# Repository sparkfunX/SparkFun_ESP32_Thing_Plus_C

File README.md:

SparkFun ESP32 Thing Plus C
========================================

[*SparkFun ESP32 Thing Plus C (SPX-18018)*](https://www.sparkfun.com/products/18018)

The [SparkFun ESP32 Thing Plus C](https://www.sparkfun.com/products/18018) is a comprehensive development platform for [Espressif's ESP32](https://espressif.com/en/products/hardware/esp32/overview). Like the 8266 and ESP32 Thing, the ESP32 Thing Plus is a **WiFi**-compatible microcontroller with support for both **Bluetooth Classic** (i.e. SPP) and **Bluetooth low-energy** (i.e. BLE, BT4.0, Bluetooth Smart), a Qwiic connector, and 21 I/O pins. Add to that a rich set of peripherals ranging from capacitive touch sensors, Hall sensors, SD card interface, Ethernet, high-speed SPIs, UARTs, I2S and I<sup>2</sup>C.

We took all the good from the original [ESP32 Thing Plus](https://www.sparkfun.com/products/15663) and sprinkled on some more! USB C provides up to 2A, upgraded 16MB flash ESP32 WROOM module, CH340 USB to serial IC, an onboard fuel gauge IC will make sure you know your battery levels, and an onboard addressable LED is perfect for as a multi-status LED. Oh, and the new taller reset and boot buttons are *so* much easier to push!

We added a dedicator regulator to the Qwiic connector to enable software power control of the Qwiic bus - great for low power logging! There's even a microSD connector on the back!

The ESP32 Thing plus integrates a rich set of peripherals, ranging from capacitive touch sensors, Hall sensors, SD card interface, Ethernet, high-speed SPI, UART, I2S and I2C. Thanks to the onboard ESP32 WROOM module, the SparkFun Thing Plus features 16MB of flash memory, 520kB of internal SRAM, an integrated 802.11 BGN WiFi transceiver and dual-mode Bluetooth capabilities, and a JST connector to plug in a LiPo battery.

For programming, select the 'ESP32 Dev Module'. This will get you direct pin to pin access to each of the WROOM's pins.

Repository Contents
-------------------

* **/Hardware** - Eagle design files (.brd, .sch)
* **/Firmware** - Example sketches demostrating extra peripherals

License Information
-------------------

This product is _**open source**_! 

Please review the LICENSE.md file for license information. 

If you have any questions or concerns on licensing, please contact technical support on our [SparkFun forums](https://forum.sparkfun.com/viewforum.php?f=152).

Distributed as-is; no warranty is given.

- Your friends at SparkFun.

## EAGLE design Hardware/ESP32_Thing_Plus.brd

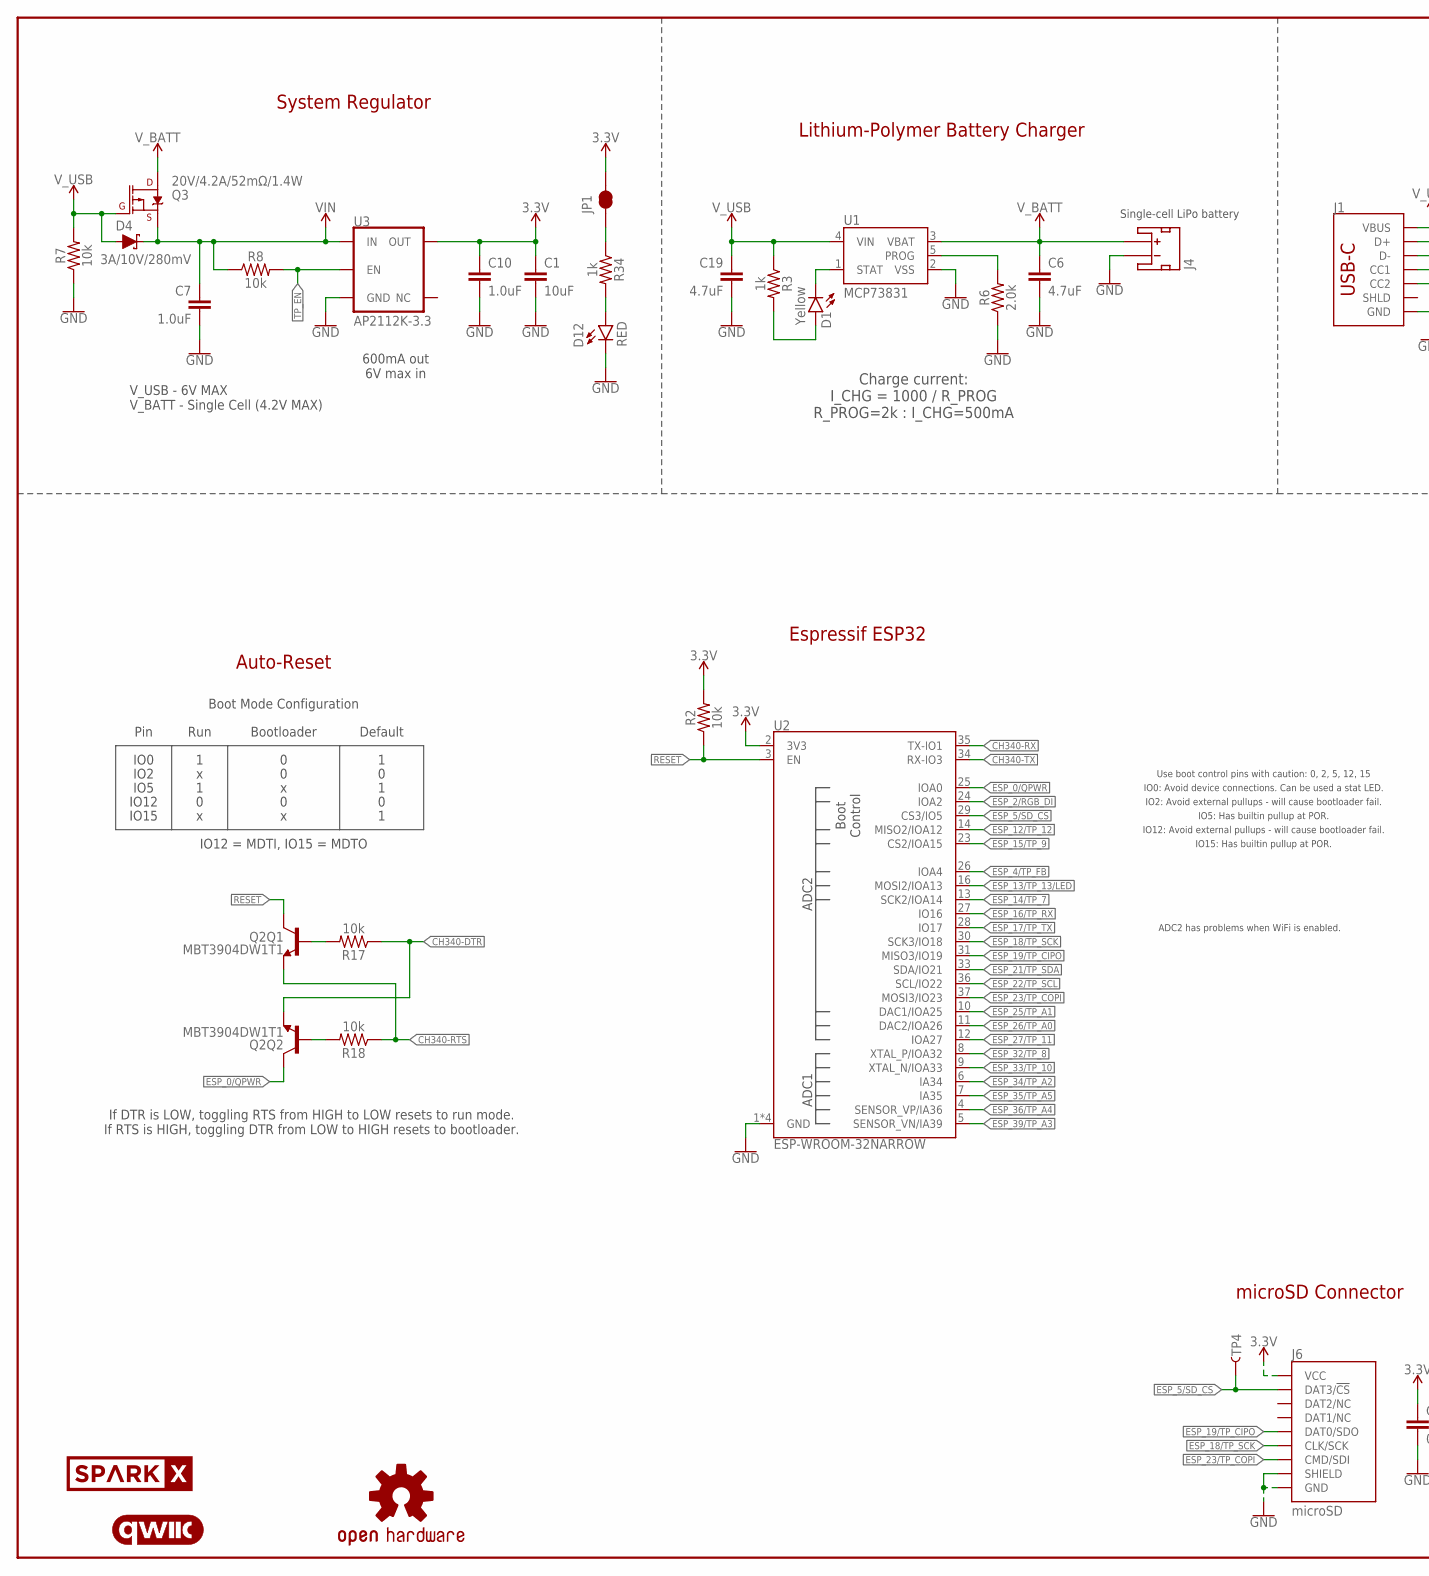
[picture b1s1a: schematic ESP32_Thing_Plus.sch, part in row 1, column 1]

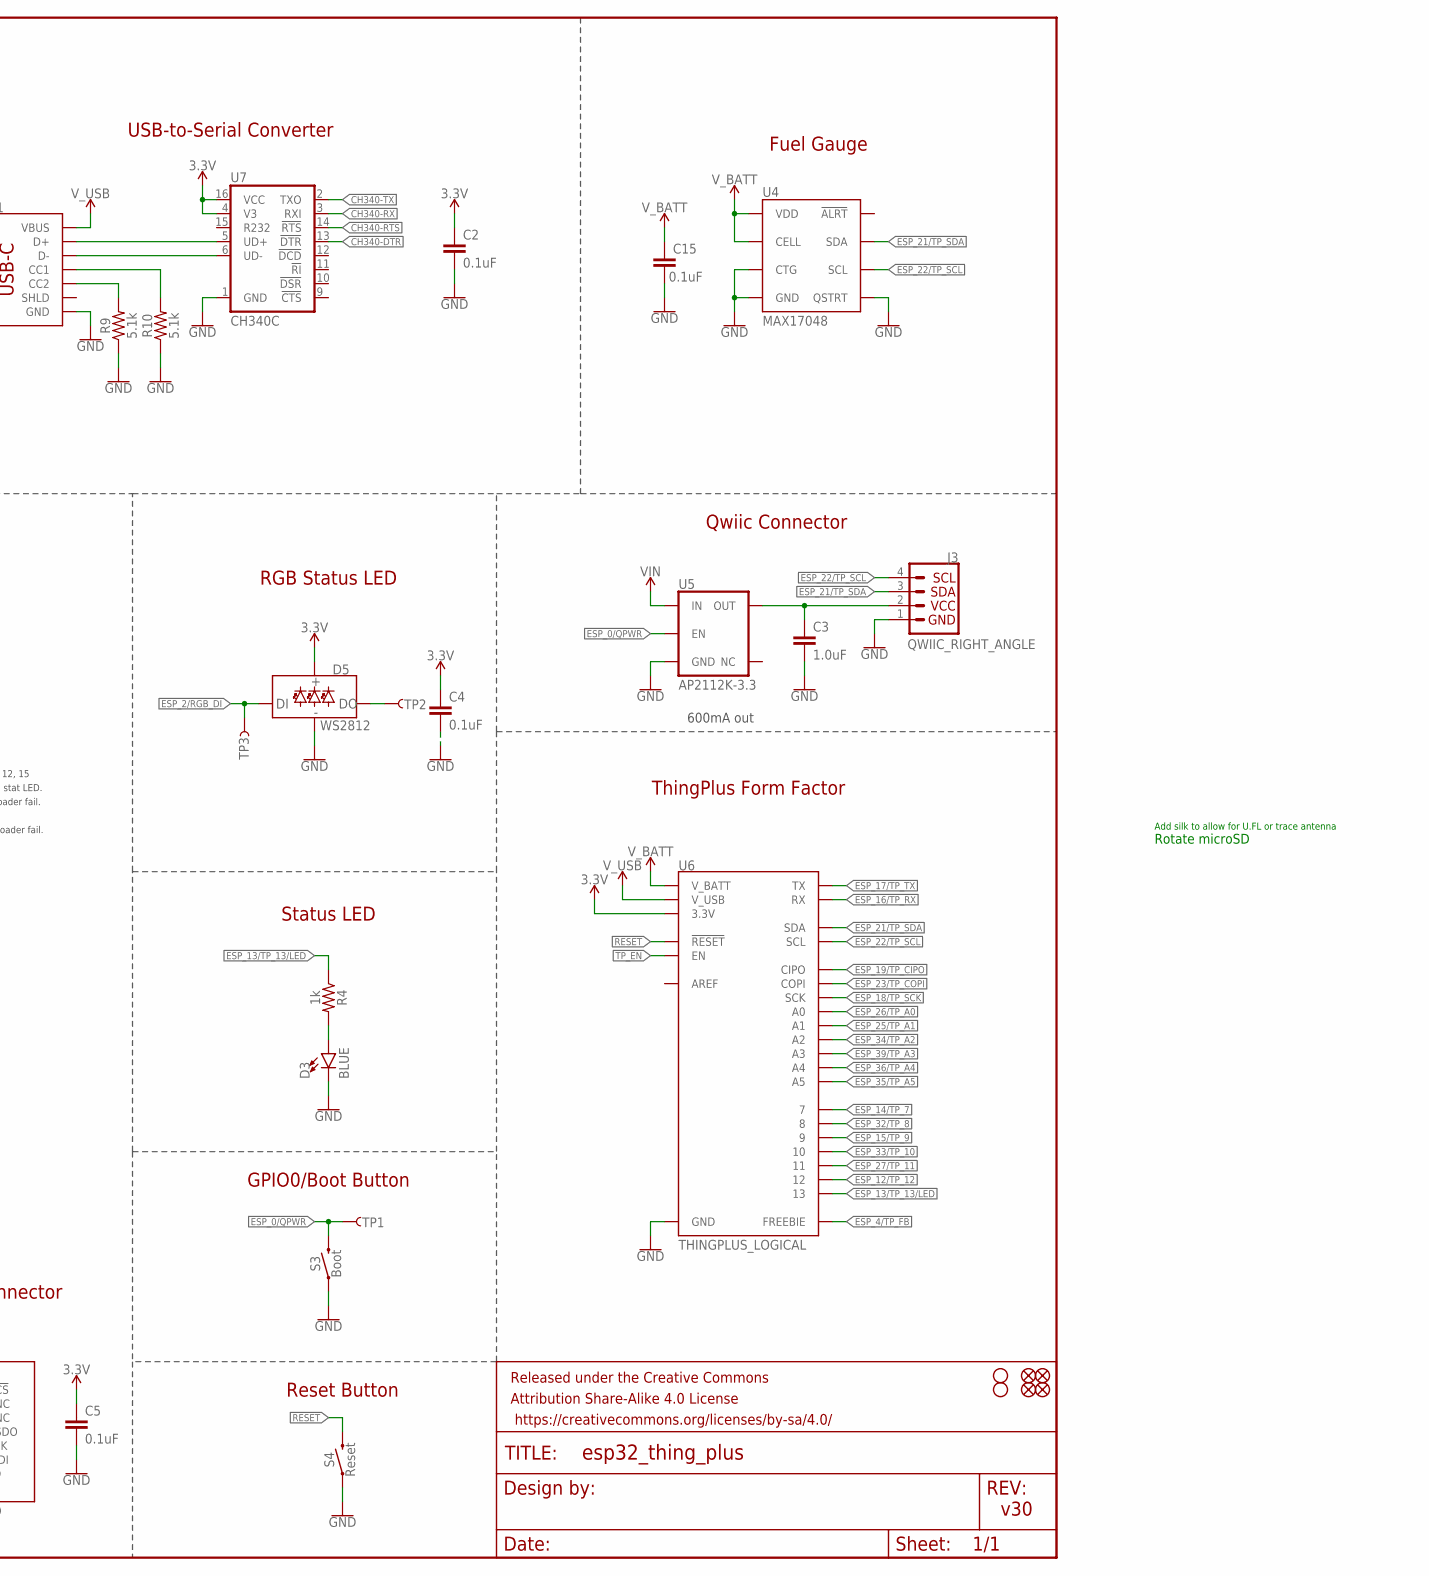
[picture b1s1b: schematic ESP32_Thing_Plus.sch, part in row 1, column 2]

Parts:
C1: 10uF; 0402-TIGHT
C2, C4, C5, C15: 0.1uF; 0402-TIGHT
C3, C7, C10: 1.0uF; 0402-TIGHT
C6: 4.7uF; 0402-TIGHT
C19: 4.7uF; 0603
D1: Yellow; LED-0603
D3: BLUE; LED-0603
D4: 3A/10V/280mV; SOD-323
D5: WS2812; WS2812-2020
D12: RED; LED-0603
FD1, FD2, FD3, FD4: FIDUCIALUFIDUCIAL; FIDUCIAL-MICRO
FRAME1: FRAME-LEDGER; CREATIVE_COMMONS
H1, H2: STAND-OFFTIGHT; STAND-OFF-TIGHT
J1: USB_C_2-LAYER_PADS; USB-C-16P-2LAYER-PADS
J3: QWIIC_RIGHT_ANGLE; JST04_1MM_RA
J4: JST_2MM_MALE; JST-2-SMD
J6: microSD; MICRO-SD-SOCKET
JP1: JUMPER-SMT_2_NC_TRACE_SILK; SMT-JUMPER_2_NC_TRACE_SILK
LOGO2: OSHW-LOGOMINI; OSHW-LOGO-MINI
LOGO4: QWIIC_LOGO_4MM; QWIIC_4MM
Q2: MBT3904DW1T1; SC70-6
Q3: 20V/4.2A/52mΩ/1.4W; SOT23-3
R2, R7, R8, R17, R18: 10k; 0402-TIGHT
R3, R4, R34: 1k; 0402-TIGHT
R6: 2.0k; 0603
R9, R10: 5.1k; 0402-TIGHT
S3: Boot; TACTILE_SWITCH_SMD_4.6X2.8MM
S4: Reset; TACTILE_SWITCH_SMD_4.6X2.8MM
TP1, TP2, TP3, TP4: TEST-POINT3X5; PAD.03X.05
U1: MCP73831; SOT23-5
U2: ESP-WROOM-32NARROW; ESP-WROOM-32-NARROW
U3, U5: AP2112K-3.3; SOT23-5
U4: MAX17048; DFN-8
U6: THINGPLUS_LOGICAL; THINGPLUS_FOOTPRINT
U7: CH340C; SO016
U$1: SPARKX-LOGO4; SPARKX-MEDIUM

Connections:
3.3V: C1.1, C2.1, C4.1, C5.1, C10.1, D5.VCC, J6.VCC, JP1.2, R2.2, U2.2 (3V3), U3.5 (OUT), U6.3V3 (3.3V), U7.4 (V3), U7.16 (VCC)
!RESET!: Q2.3 (C), R2.1, S4.3 (2), S4.4 (2), U2.3 (EN), U6.RST (!RESET)
CH340-DTR: Q2.1 (E), R17.1, U7.13 (!DTR)
CH340-RTS: Q2.4 (E), R18.1, U7.14 (!RTS)
CH340-RX: U2.35 (TX-IO1), U7.3 (RXI)
CH340-TX: U2.34 (RX-IO3), U7.2 (TXO)
CHG: D1.C, U1.1 (STAT)
CHG_LED: D1.A, R3.2
D+: J1.A6 (D+), J1.B6 (D+), U7.5 (UD+)
D-: J1.A7 (D-), J1.B7 (D-), U7.6 (UD-)
DTR-10K: Q2.5 (B), R17.2
ESP_0/QPWR: Q2.6 (C), S3.3 (2), S3.4 (2), TP1.P$1, U2.25 (IOA0), U5.3 (EN)
ESP_2/RGB_DI: D5.DI, TP3.P$1, U2.24 (IOA2)
ESP_4/TP_FB: U2.26 (IOA4), U6.FREEBIE
ESP_5/SD_CS: J6.CS/DAT3 (DAT3/!CS!), TP4.P$1, U2.29 (CS3/IO5)
ESP_12/TP_12: U2.14 (MISO2/IOA12), U6.12
ESP_13/TP_13/LED: R4.1, U2.16 (MOSI2/IOA13), U6.13
ESP_14/TP_7: U2.13 (SCK2/IOA14), U6.7
ESP_15/TP_9: U2.23 (CS2/IOA15), U6.9
ESP_16/TP_RX: U2.27 (IO16), U6.RX
ESP_17/TP_TX: U2.28 (IO17), U6.TX
ESP_18/TP_SCK: J6.SCLK (CLK/SCK), U2.30 (SCK3/IO18), U6.SCK
ESP_19/TP_CIPO: J6.DO/DAT0 (DAT0/SDO), U2.31 (MISO3/IO19), U6.CIPO
ESP_21/TP_SDA: J3.3, U2.33 (SDA/IO21), U4.8 (SDA), U6.SDA
ESP_22/TP_SCL: J3.4, U2.36 (SCL/IO22), U4.7 (SCL), U6.SCL
ESP_23/TP_COPI: J6.DI/CMD (CMD/SDI), U2.37 (MOSI3/IO23), U6.COPI
ESP_25/TP_A1: U2.10 (DAC1/IOA25), U6.A1
ESP_26/TP_A0: U2.11 (DAC2/IOA26), U6.A0
ESP_27/TP_11: U2.12 (IOA27), U6.11
ESP_32/TP_8: U2.8 (XTAL_P/IOA32), U6.8
ESP_33/TP_10: U2.9 (XTAL_N/IOA33), U6.10
ESP_34/TP_A2: U2.6 (IA34), U6.A2
ESP_35/TP_A5: U2.7 (IA35), U6.A5
ESP_36/TP_A4: U2.4 (SENSOR_VP/IA36), U6.A4
ESP_39/TP_A3: U2.5 (SENSOR_VN/IA39), U6.A3
GND: C1.2, C2.2, C3.2, C4.2, C5.2, C6.2, C7.2, C10.2, C15.2, C19.2, D3.C, D5.GND, D12.C, J1.GND, J1.GND2 (GND), J3.1, J4.1 (-), J6.CD1 (SHIELD), J6.GND, J6.GND1 (GND), J6.GND3 (GND), R6.1, R7.1, R9.1, R10.1, S3.1, S3.2 (1), S4.1, S4.2 (1), U1.2 (VSS), U2.1 (GND), U2.15 (GND), U2.38 (GND), U2.GND, U3.2 (GND), U4.1 (CTG), U4.4 (GND), U4.6 (QSTRT), U4.9 (GND), U5.2 (GND), U6.GND, U7.1 (GND)
unnamed: JP1.1, R34.1
unnamed: D3.A, R4.2
unnamed: D5.DO, TP2.P$1
unnamed: J1.B5 (CC2), R9.2
unnamed: J1.A5 (CC1), R10.2
unnamed: R6.2, U1.5 (PROG)
unnamed: D12.A, R34.2
QWIIC_PWR: C3.1, J3.2, U5.5 (OUT)
RTS-10K: Q2.2 (B), R18.2
TP_EN: R8.2, U3.3 (EN), U6.EN
VIN: C7.1, D4.C, Q3.2 (S), R8.1, U3.1 (IN), U5.1 (IN)
V_BATT: C6.1, C15.1, J4.2 (+), Q3.3 (D), U1.3 (VBAT), U4.2 (CELL), U4.3 (VDD), U6.V_BATT
V_USB: C19.1, D4.A, J1.VBUS1 (VBUS), J1.VBUS2 (VBUS), Q3.1 (G), R3.1, R7.2, U1.4 (VIN), U6.V_USB

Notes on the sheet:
USB-to-Serial Converter
Single-cell LiPo battery
Charge current: I_CHG = 1000 / R_PROG R_PROG=2k : I_CHG=500mA
System Regulator
Lithium-Polymer Battery Charger
600mA out 6V max in
Auto-Reset
Espressif ESP32
Reset Button
ThingPlus Form Factor
v30
If DTR is LOW, toggling RTS from HIGH to LOW resets to run mode. If RTS is HIGH, toggling DTR from LOW to HIGH resets to bootloader.
Qwiic Connector
Status LED
GPIO0/Boot Button
V_USB - 6V MAX V_BATT - Single Cell (4.2V MAX)
Pin
IO0
IO2
IO12
IO15
IO5
Run
Bootloader
Default
IO12 = MDTI, IO15 = MDTO
Boot Mode Configuration
IO0: Avoid device connections. Can be used a stat LED.
ADC2 has problems when WiFi is enabled.
IO12: Avoid external pullups - will cause bootloader fail.
Use boot control pins with caution: 0, 2, 5, 12, 15
IO2: Avoid external pullups - will cause bootloader fail.
Fuel Gauge
600mA out
RGB Status LED
microSD Connector
Add silk to allow for U.FL or trace antenna
IO15: Has builtin pullup at POR.
IO5: Has builtin pullup at POR.
Rotate microSD

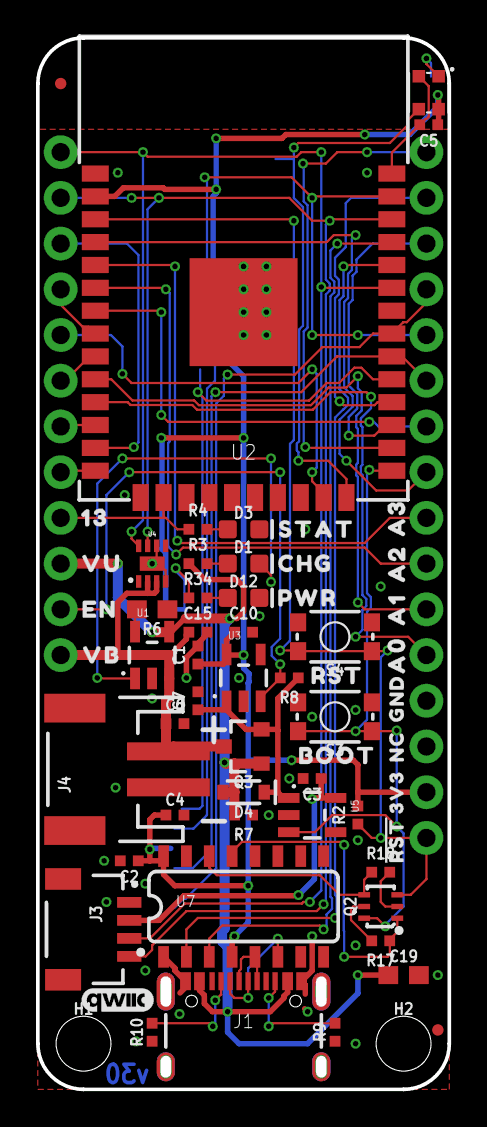
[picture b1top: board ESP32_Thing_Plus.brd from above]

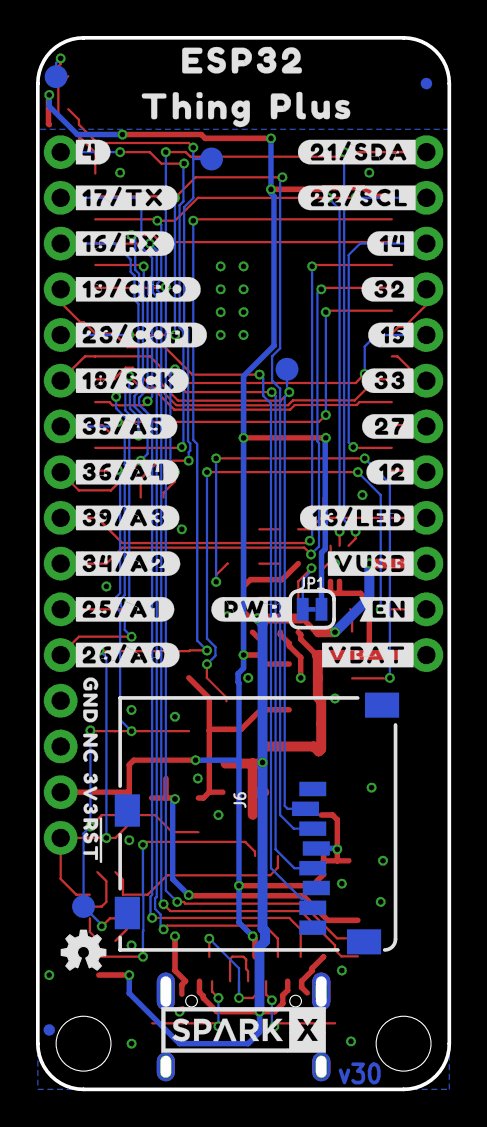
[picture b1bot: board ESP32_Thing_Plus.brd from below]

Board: 2 copper layers, 22.5 x 58.0 mm, 106 parts (42 on the bottom side), 49 nets.

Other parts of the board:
U$23, U$108: 3V30
U$24: CHG1
U$25: PWR2
U$26: STAT0
U$56, U$75: GND1
U$57: #4#0
U$59: ORDERING_INSTRUCTIONS
U$62: #23#COPI#0
U$68: A03
U$69: A12
U$70: A21
U$71: A30
U$72: #17#TX#0
U$73: VB1
U$74: EN3
U$76: VU0
U$77: 130
U$78: BOOT0
U$79, U$109: #RST#0
U$80: RST0
U$81: #16#RX#0
U$82: #19#CIPO#0
U$83: #18#SCK#0
U$84: #35#A5#0
U$85: #36#A4#0
U$86: #25#A1#2
U$87: #26#A0#3
U$88: #34#A2#1
U$89: #39#A3#0
U$90: #12#4
U$91: #14#9
U$92: #15#7
U$93: #27#5
U$94: #32#8
U$95: #33#6
U$96: #EN#1
U$97: #VBAT#0
U$98: #VUSB#2
U$99: #13#LED#0
U$100: #21#SDA#1
U$101: #22#SCL#0
U$102: #PWR#0
U$103: ESP320
U$104: THING1
U$105: PLUS2
U$106, U$107: NC0

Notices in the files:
parts and their libraries:
SparkFun-Resistors: Licensing: Creative Commons ShareAlike 4.0 International - https://creativecommons.org/licenses/by-sa/4.0
SparkFun-Aesthetics: Released under the Creative Commons Attribution Share-Alike 4.0 License
SparkFun-Aesthetics: https://creativecommons.org/licenses/by-sa/4.0
